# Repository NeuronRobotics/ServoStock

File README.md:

ServoStock
==========

This is the repository for the bowler enabled, closed loop controlled 3d printer. This repository is for all of the code for the printer.

# Control Application

From Eclipse for Java

* https://github.com/NeuronRobotics/java-bowler
* https://github.com/NeuronRobotics/NrConsole
* Jmonkey Game Engine

# Dependancies

## Compiler and c-bowler
Clone the c-bowler repository and install the compilers from here:

* https://github.com/NeuronRobotics/c-bowler

##MPLabx

Install MPLABX from here:

http://www.microchip.com/pagehandler/en-us/family/mplabx/

# Opening projects

Both repositoried should be in the same folder on your disk.

Open c-bowler in MPLABX

```
c-bowler/firmware/library/NR-Clib/development/c-bowler.X
```

And the ServoStock Code

```
ServoStock/firmware/MplabX_Projects/ServoPrinterController.X
```

You are ready to build and program.

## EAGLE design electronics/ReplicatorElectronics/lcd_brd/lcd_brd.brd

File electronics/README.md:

These are the assembly instructions for the ServoStock Electronics platform

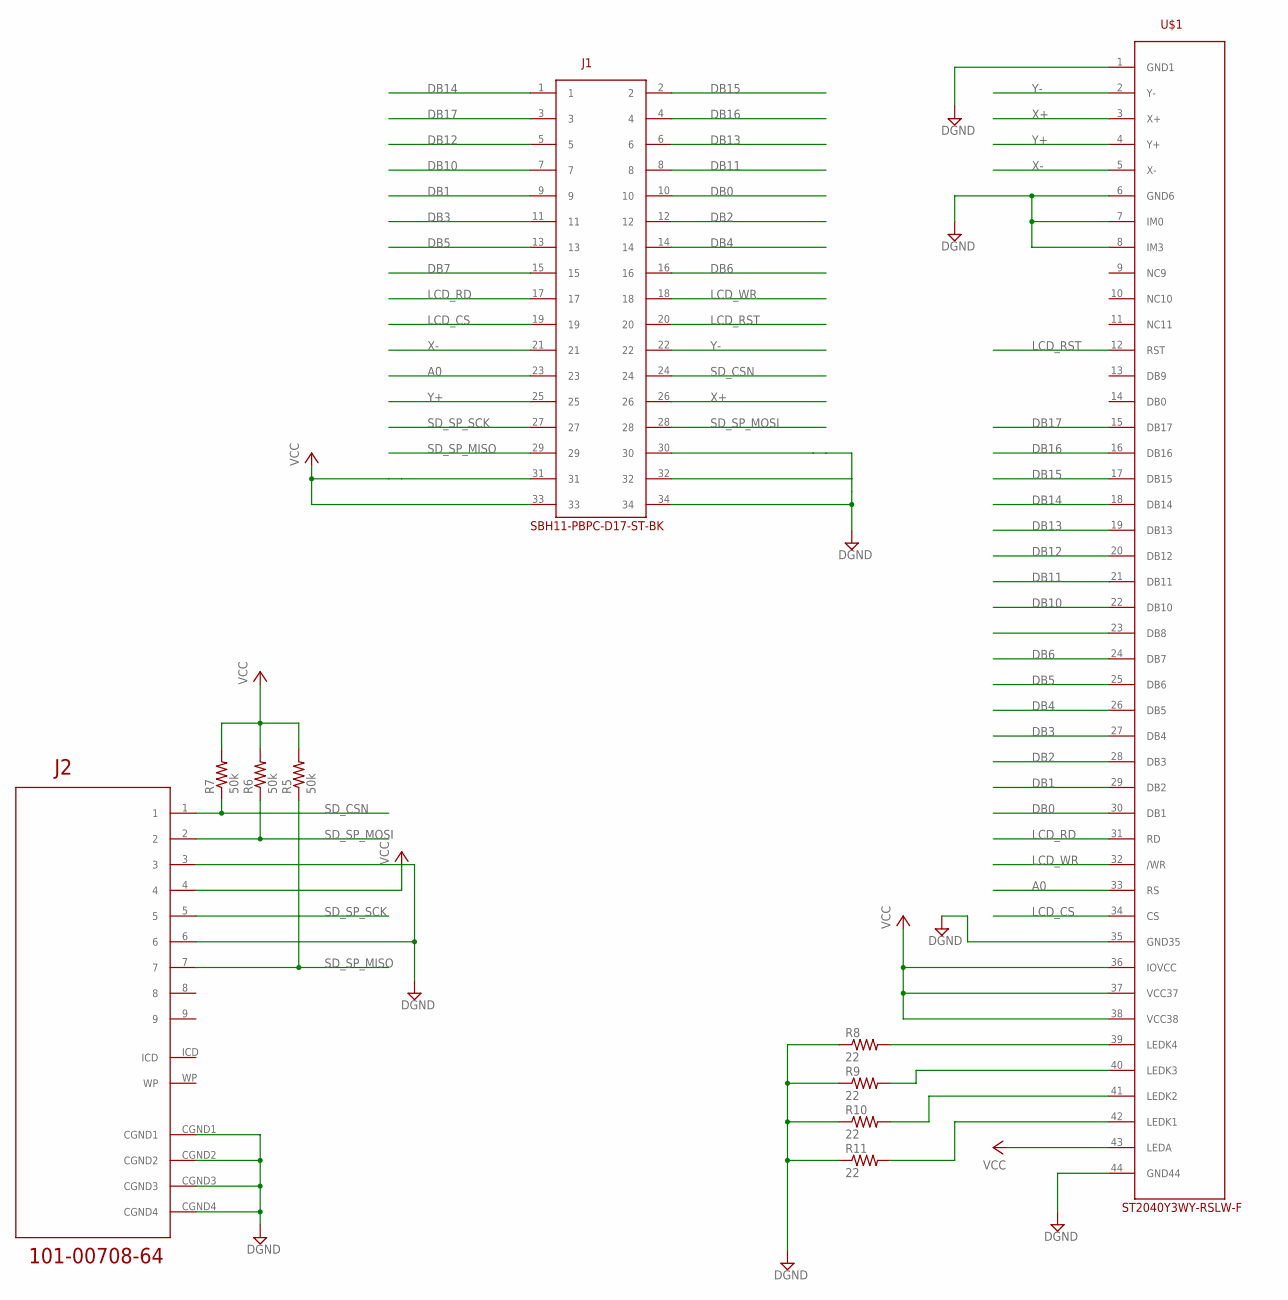
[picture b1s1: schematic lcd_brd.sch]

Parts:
J1: SBH11-PBPC-D17-ST-BK
J2: 101-00708-64
R5, R6, R7: 50k; R0603
R8, R9, R10, R11: 22; R0603
U$1: ST2040Y3WY-RSLW-F; ST0240Y3WY-RSLW-F

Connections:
A0: J1.23, U$1.33 (RS)
DB0: J1.10, U$1.30 (DB1)
DB1: J1.9, U$1.29 (DB2)
DB2: J1.12, U$1.28 (DB3)
DB3: J1.11, U$1.27 (DB4)
DB4: J1.14, U$1.26 (DB5)
DB5: J1.13, U$1.25 (DB6)
DB6: J1.16, U$1.24 (DB7)
DB7: J1.15, U$1.23 (DB8)
DB10: J1.7, U$1.22 (DB10)
DB11: J1.8, U$1.21 (DB11)
DB12: J1.5, U$1.20 (DB12)
DB13: J1.6, U$1.19 (DB13)
DB14: J1.1, U$1.18 (DB14)
DB15: J1.2, U$1.17 (DB15)
DB16: J1.4, U$1.16 (DB16)
DB17: J1.3, U$1.15 (DB17)
DGND: J1.30, J1.32, J1.34, J2.3, J2.6, J2.CGND1, J2.CGND2, J2.CGND3, J2.CGND4, R8.1, R9.1, R10.1, R11.1, U$1.1 (GND1), U$1.6 (GND6), U$1.7 (IM0), U$1.8 (IM3), U$1.35 (GND35), U$1.44 (GND44)
LCD_CS: J1.19, U$1.34 (CS)
LCD_RD: J1.17, U$1.31 (RD)
LCD_RST: J1.20, U$1.12 (RST)
LCD_WR: J1.18, U$1.32 (/WR)
unnamed: R8.2, U$1.39 (LEDK4)
unnamed: R9.2, U$1.40 (LEDK3)
unnamed: R10.2, U$1.41 (LEDK2)
unnamed: R11.2, U$1.42 (LEDK1)
SD_CSN: J1.24, J2.1, R7.1
SD_SP_MISO: J1.29, J2.7, R5.1
SD_SP_MOSI: J1.28, J2.2, R6.1
SD_SP_SCK: J1.27, J2.5
VCC: J1.31, J1.33, J2.4, R5.2, R6.2, R7.2, U$1.36 (IOVCC), U$1.37 (VCC37), U$1.38 (VCC38), U$1.43 (LEDA)
X+: J1.26, U$1.3 (X+)
X-: J1.21, U$1.5 (X-)
Y+: J1.25, U$1.4 (Y+)
Y-: J1.22, U$1.2 (Y-)

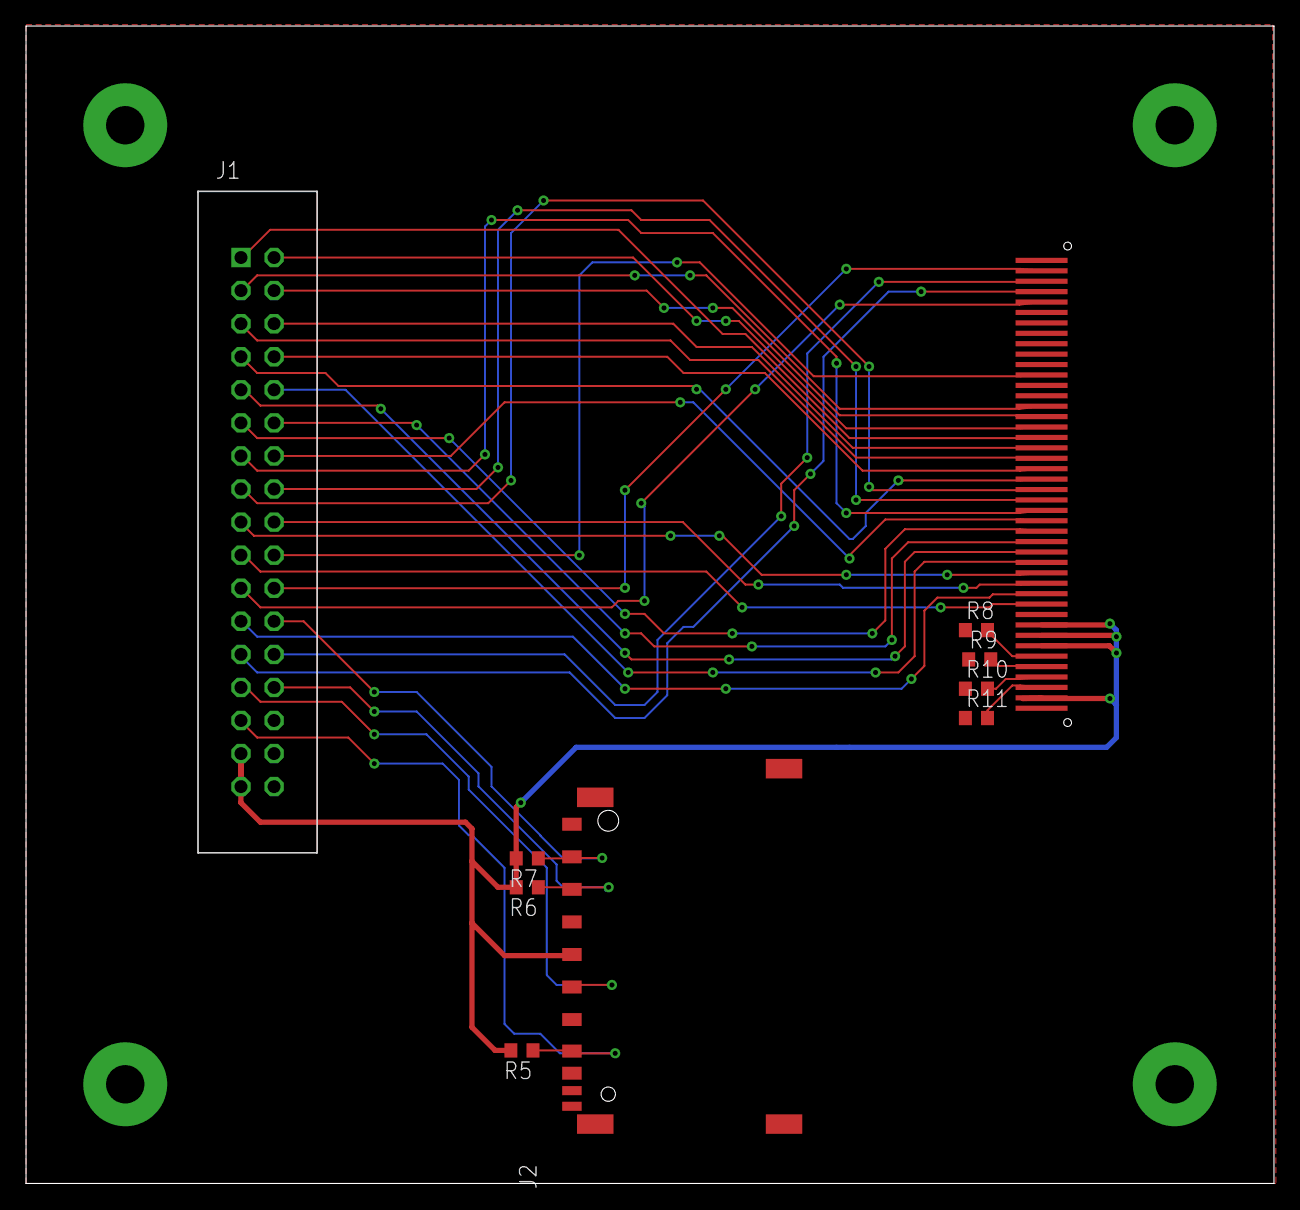
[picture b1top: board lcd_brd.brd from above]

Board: 2 copper layers, 95.8 x 88.9 mm, 10 parts (0 on the bottom side), 35 nets.

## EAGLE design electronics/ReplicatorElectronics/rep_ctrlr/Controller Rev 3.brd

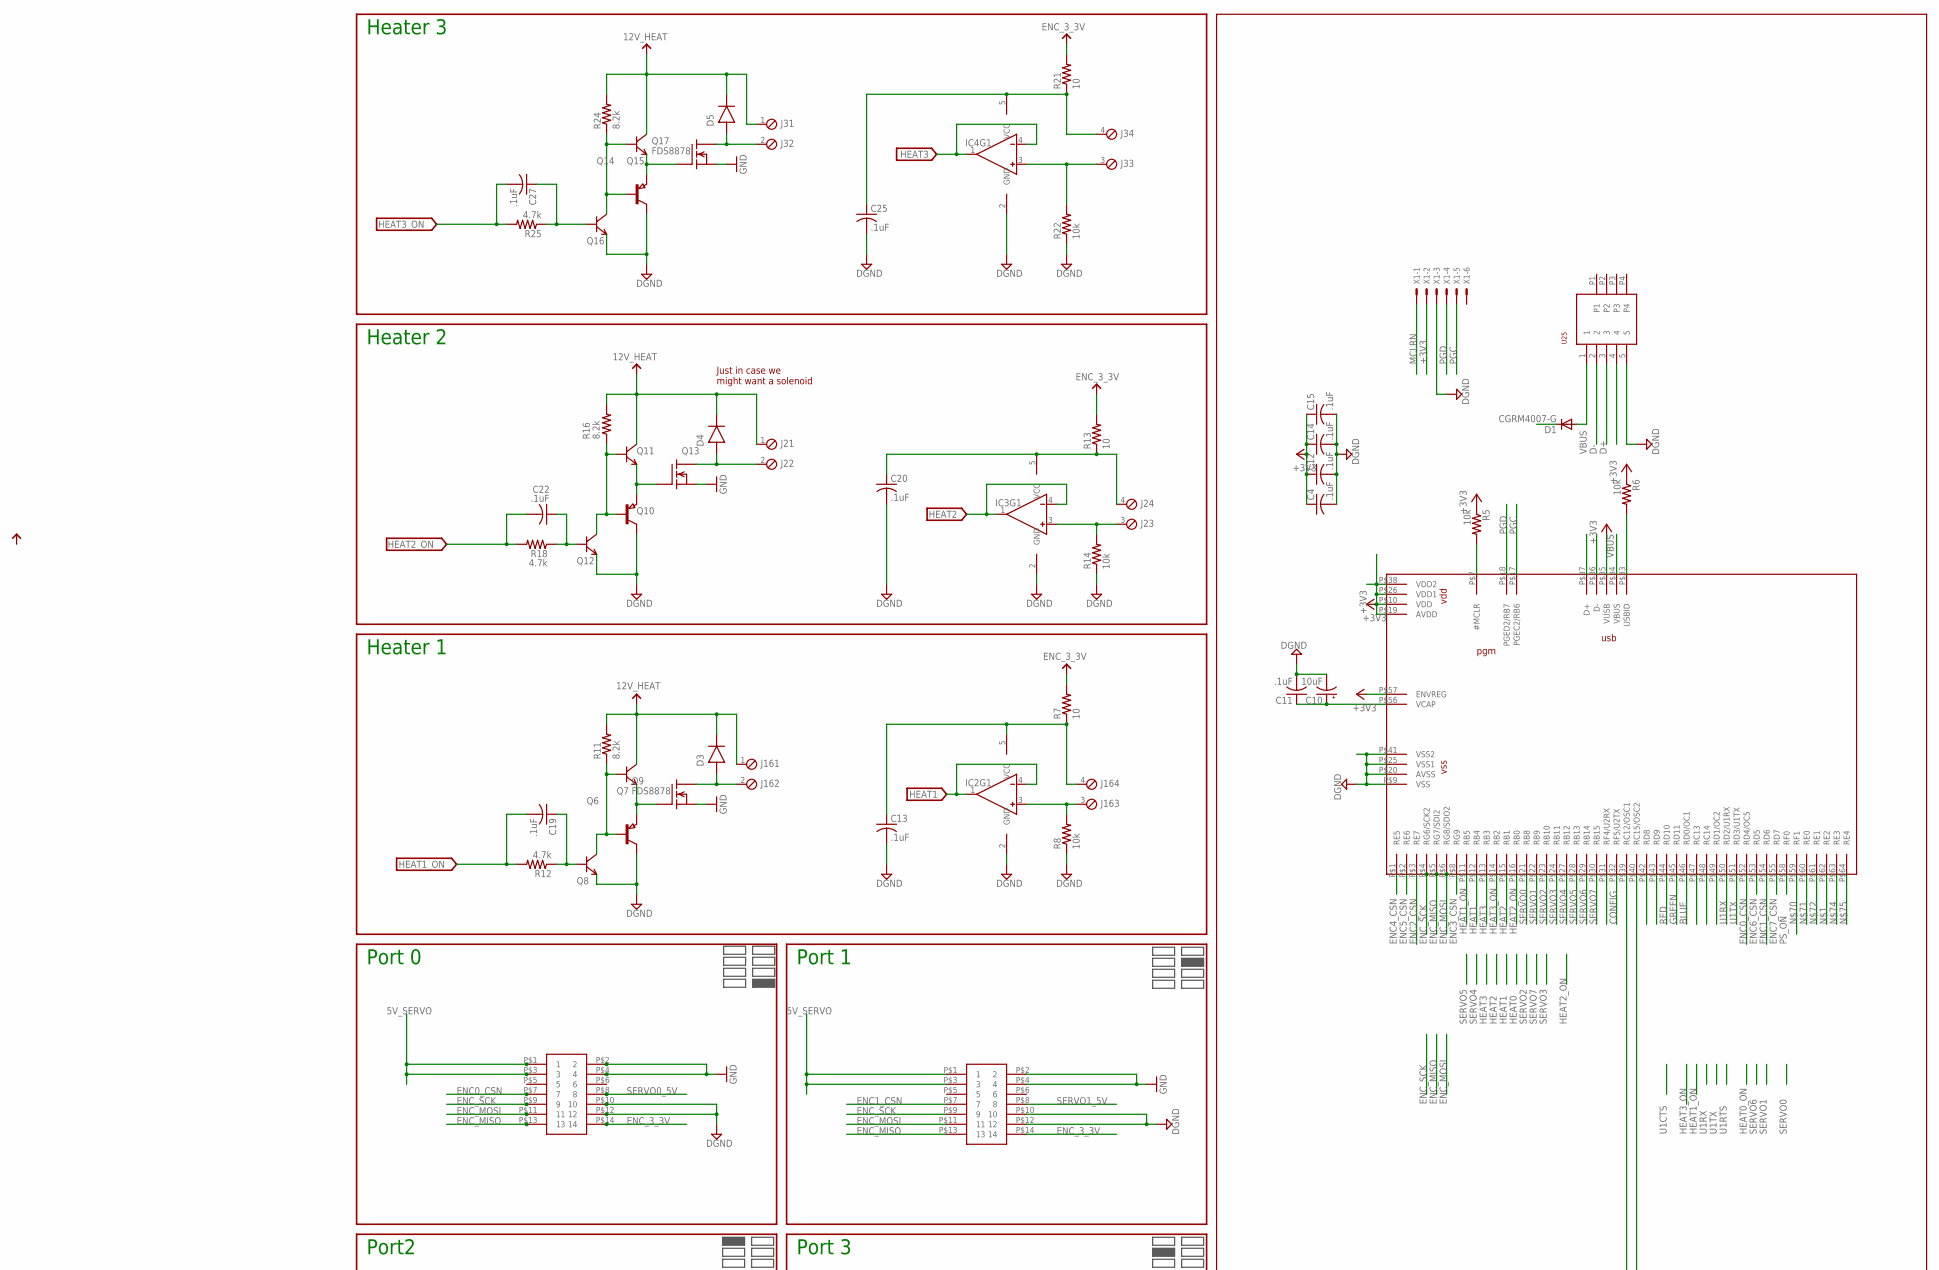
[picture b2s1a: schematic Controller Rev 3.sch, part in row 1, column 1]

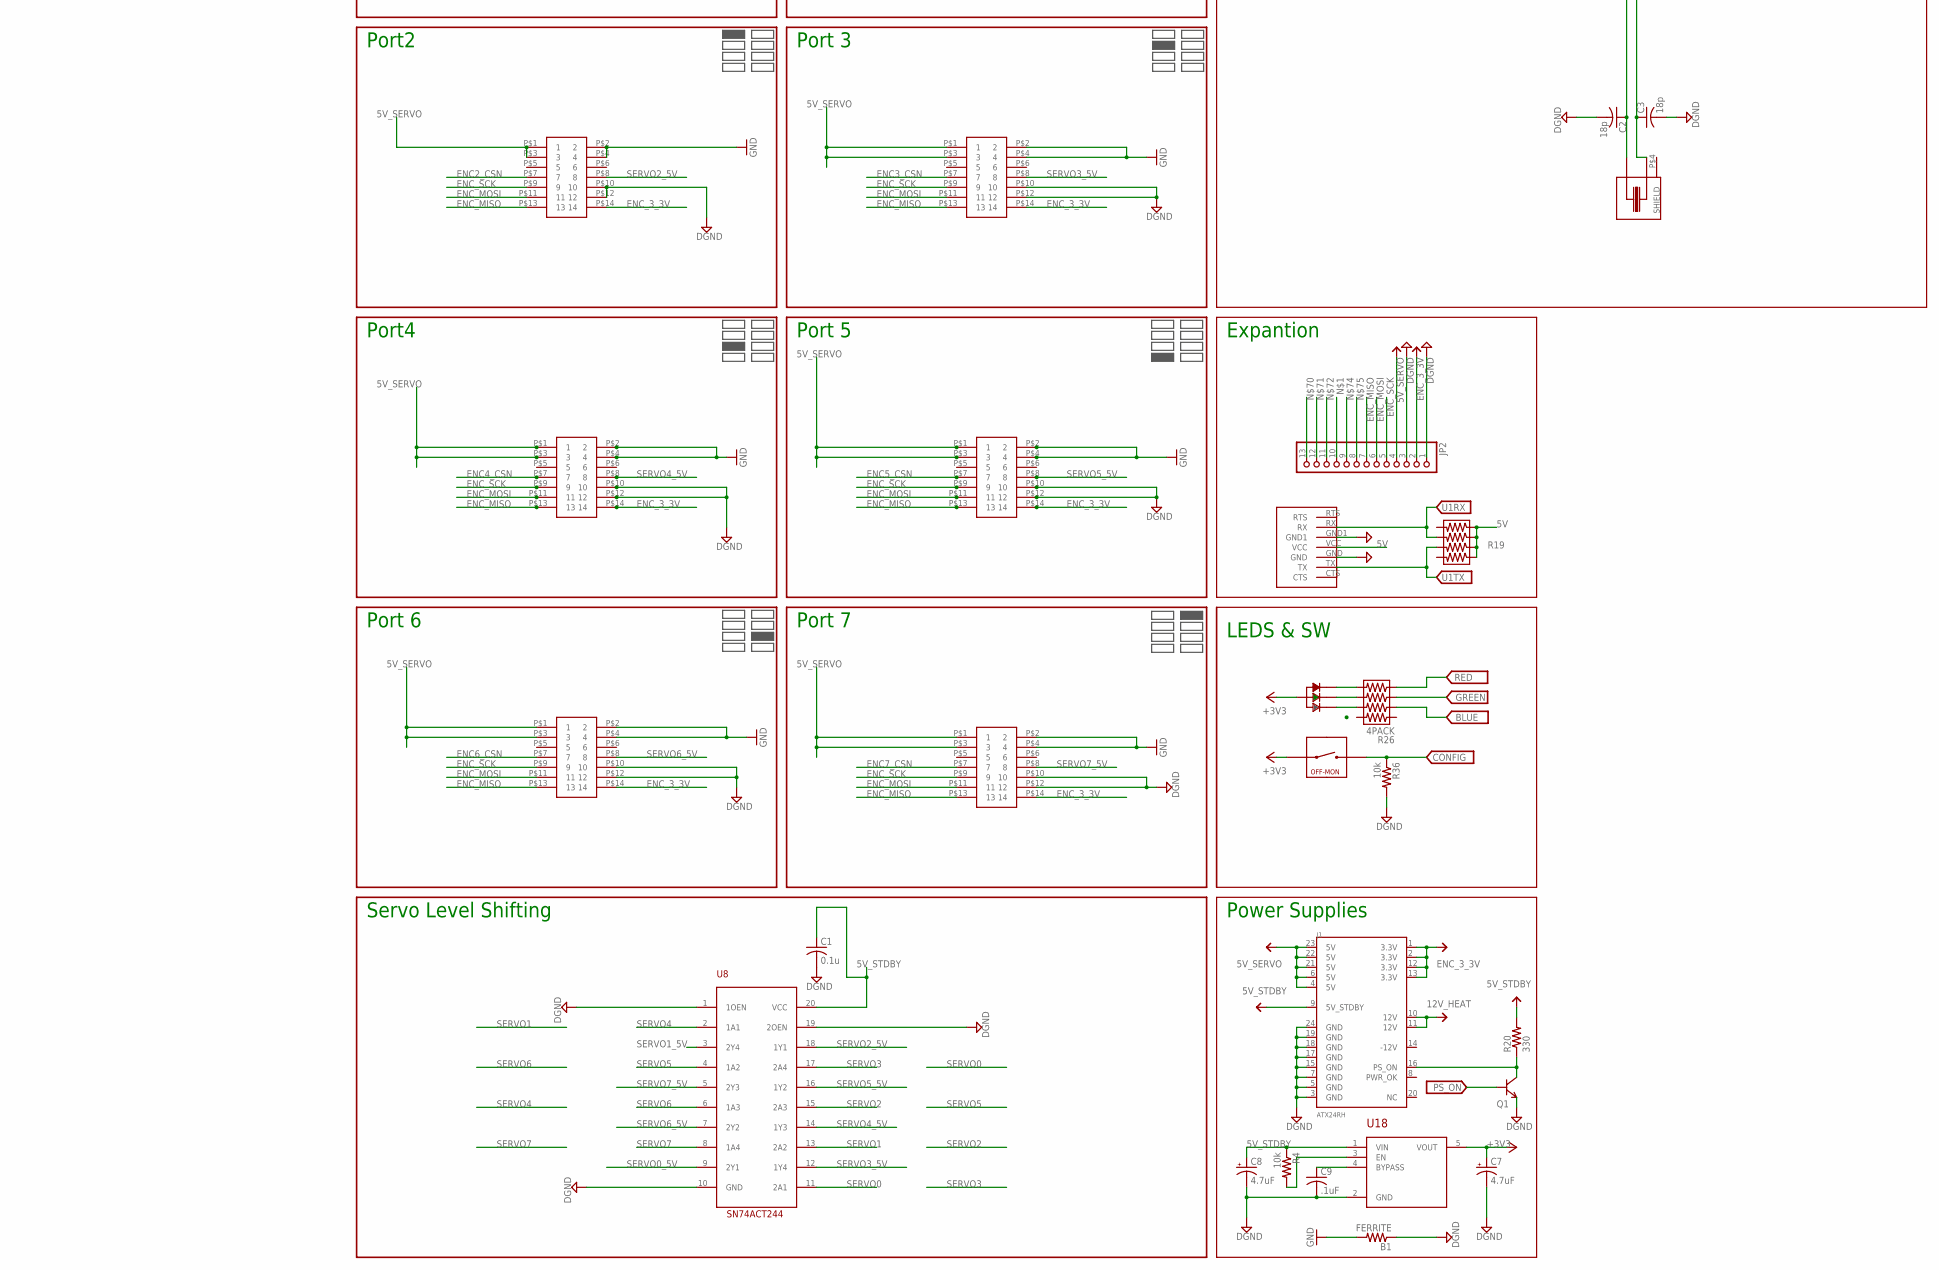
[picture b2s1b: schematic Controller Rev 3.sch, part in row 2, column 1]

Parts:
B1: FERRITE; R0603
C1: 0.1u; C0402
C2, C3: 18p; C0603
C4, C11, C12, C13, C14, C15, C19, C20, C22, C25, C27: .1uF; C0603
C7, C8: 4.7uF; R/2012-12R
C9: .1uF; C0402
C10: 10uF; R/2012-12R
D1: CGRM4007-G; SOD-123_MINI-SMA
D3, D4, D5: DISCRETE_DIODESMA; DISCRETE_SMA
IC2, IC3, IC4: MICROCHIP_MCP6001-LT; MICROCHIP_SC70-5-LT
J1: ATX24RH; ATX24_RIGHT_ANGLE
J2, J3, J16: OSTVN04A150; 4POL254
J10: WASP7PIN
JP2: PINHD-1X13_BIG; 1X13-BIG
Q1, Q7, Q8, Q11, Q12, Q15, Q16: DISCRETE_MMBT3904LT1G; DISCRETE_SOT23
Q6, Q10, Q14: PNP-TRANSISTOR_SOT23; SOT23
Q9, Q13, Q17: FDS8878; SO-8
R4: 10k; R0402
R5, R6, R8, R14, R22, R36: 10k; R0603
R7, R13, R21: 10; R0603
R11, R16, R24: 8.2k; R0603
R12, R18, R25: 4.7k; R0603
R19, R26: 4PACK; 4PACK_0603
R20: 330; R0603
SW3: SPST; B3U-1000P
U1: TRI-LED-SMD; TRI_LED_SMD
U3: PIC32-64TQFP64-2; TQFP64-2
U8: SN74ACT244; 20-SOIC
U18: LDS3985XX33; SOT23-5
U25: 1734035-1_USB; 1734035-1_1734035
U$1, U$2, U$3, U$4, U$5, U$6, U$7, U$8: SBH11-NBPC-D07-SM-BK
X1: 22-23-2061
X2: CMR3XXT; CMR309T

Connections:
5V: J10.VCC, R19.R1B, R19.R2B, R19.R3B, R19.R4B
5V_SERVO: J1.4 (5V), J1.6 (5V), J1.21 (5V), J1.22 (5V), J1.23 (5V), JP2.4, U$1.P$1 (1), U$1.P$3 (3), U$2.P$1 (1), U$2.P$3 (3), U$3.P$1 (1), U$3.P$3 (3), U$4.P$1 (1), U$4.P$3 (3), U$5.P$1 (1), U$5.P$3 (3), U$6.P$1 (1), U$6.P$3 (3), U$7.P$1 (1), U$7.P$3 (3), U$8.P$1 (1), U$8.P$3 (3)
5V_STDBY: C1.1, C8.+, D1.C, J1.9 (5V_STDBY), R4.1, R20.2, U8.20 (VCC), U18.1 (VIN)
12V_HEAT: D3.C, D4.C, D5.C, J1.10 (12V), J1.11 (12V), J2.1, J3.1, J16.1, Q7.3 (C), Q11.3 (C), Q15.3 (C), R11.2, R16.2, R24.2
12V_SW1: D3.A, J16.2, Q9.5 (D), Q9.6 (D), Q9.7 (D), Q9.8 (D)
12V_SW2: D4.A, J2.2, Q13.5 (D), Q13.6 (D), Q13.7 (D), Q13.8 (D)
12V_SW3: D5.A, J3.2, Q17.5 (D), Q17.6 (D), Q17.7 (D), Q17.8 (D)
+3V3: C4.1, C7.+, C12.1, C14.1, C15.1, R5.1, R6.1, SW3.P$1, U1.COMM-A, U3.P$10 (VDD), U3.P$19 (AVDD), U3.P$26 (VDD1), U3.P$35 (VUSB), U3.P$38 (VDD2), U3.P$57 (ENVREG), U18.5 (VOUT), X1.2
B: R26.R2A, U1.BLUE
BLUE: R26.R2B, U3.P$46 (RD0/OC1)
CONFIG: R36.1, SW3.P$3, U3.P$32 (RF5/U2TX)
D+: U3.P$37 (D+), U25.3
D-: U3.P$36 (D-), U25.2
DGND: B1.1, C1.2, C2.2, C3.2, C4.2, C7.-, C8.-, C9.2, C10.-, C11.2, C12.2, C13.2, C14.2, C15.2, C20.2, C25.2, IC2.2 (GND), IC3.2 (GND), IC4.2 (GND), J1.3 (GND), J1.5 (GND), J1.7 (GND), J1.15 (GND), J1.17 (GND), J1.18 (GND), J1.19 (GND), J1.24 (GND), J10.GND, J10.GND1, JP2.1, JP2.3, Q1.2 (E), Q6.3 (C), Q8.2 (E), Q10.3 (C), Q12.2 (E), Q14.3 (C), Q16.2 (E), R8.1, R14.1, R22.1, R36.2, U3.P$9 (VSS), U3.P$20 (AVSS), U3.P$25 (VSS1), U3.P$41 (VSS2), U8.1 (1OEN), U8.10 (GND), U8.19 (2OEN), U18.2 (GND), U25.5, U$1.P$10 (10), U$1.P$12 (12), U$2.P$10 (10), U$2.P$12 (12), U$3.P$10 (10), U$3.P$12 (12), U$4.P$10 (10), U$4.P$12 (12), U$5.P$10 (10), U$5.P$12 (12), U$6.P$10 (10), U$6.P$12 (12), U$7.P$10 (10), U$7.P$12 (12), U$8.P$10 (10), U$8.P$12 (12), X1.3
ENC0_CSN: U3.P$52 (RD4/OC5), U$8.P$7 (7)
ENC1_CSN: U3.P$54 (RD6), U$6.P$7 (7)
ENC2_CSN: U3.P$3 (RE7), U$1.P$7 (7)
ENC3_CSN: U3.P$8 (RG9), U$2.P$7 (7)
ENC4_CSN: U3.P$1 (RE5), U$3.P$7 (7)
ENC5_CSN: U3.P$2 (RE6), U$4.P$7 (7)
ENC6_CSN: U3.P$53 (RD5), U$7.P$7 (7)
ENC7_CSN: U3.P$55 (RD7), U$5.P$7 (7)
ENC_3_3V: J1.1 (3.3V), J1.2 (3.3V), J1.12 (3.3V), J1.13 (3.3V), JP2.2, R7.2, R13.2, R21.2, U$1.P$14 (14), U$2.P$14 (14), U$3.P$14 (14), U$4.P$14 (14), U$5.P$14 (14), U$6.P$14 (14), U$7.P$14 (14), U$8.P$14 (14)
ENC_MISO: JP2.7, U3.P$5 (RG7/SDI2), U$1.P$13 (13), U$2.P$13 (13), U$3.P$13 (13), U$4.P$13 (13), U$5.P$13 (13), U$6.P$13 (13), U$7.P$13 (13), U$8.P$13 (13)
ENC_MOSI: JP2.6, U3.P$6 (RG8/SDO2), U$1.P$11 (11), U$2.P$11 (11), U$3.P$11 (11), U$4.P$11 (11), U$5.P$11 (11), U$6.P$11 (11), U$7.P$11 (11), U$8.P$11 (11)
ENC_SCK: JP2.5, U3.P$4 (RG6/SCK2), U$1.P$9 (9), U$2.P$9 (9), U$3.P$9 (9), U$4.P$9 (9), U$5.P$9 (9), U$6.P$9 (9), U$7.P$9 (9), U$8.P$9 (9)
G: R26.R3A, U1.GRN
GND: B1.2, Q9.1 (S), Q9.2 (S), Q9.3 (S), Q13.1 (S), Q13.2 (S), Q13.3 (S), Q17.1 (S), Q17.2 (S), Q17.3 (S), U$1.P$2 (2), U$1.P$4 (4), U$2.P$2 (2), U$2.P$4 (4), U$3.P$2 (2), U$3.P$4 (4), U$4.P$2 (2), U$4.P$4 (4), U$5.P$2 (2), U$5.P$4 (4), U$6.P$2 (2), U$6.P$4 (4), U$7.P$2 (2), U$7.P$4 (4), U$8.P$2 (2), U$8.P$4 (4)
GREEN: R26.R3B, U3.P$45 (RD11)
HEAT1: IC2.1 (OUT), IC2.4 (IN-), U3.P$12 (RB4)
HEAT1_ON: C19.2, R12.2, U3.P$11 (RB5)
HEAT2: IC3.1 (OUT), IC3.4 (IN-), U3.P$15 (RB1)
HEAT2_ON: C22.2, R18.2, U3.P$16 (RB0)
HEAT3: IC4.1 (OUT), IC4.4 (IN-), U3.P$13 (RB3)
HEAT3_ON: C27.2, R25.2, U3.P$14 (RB2)
MCLRN: R5.2, U3.P$7 (#MCLR), X1.1
unnamed: JP2.10, U3.P$62 (RE2)
unnamed: R4.2, U18.3 (EN)
unnamed: C9.1, U18.4 (BYPASS)
unnamed: C3.1, U3.P$40 (RC15/OSC2), X2.P$3
unnamed: C10.+, C11.1, U3.P$56 (VCAP)
unnamed: C2.1, U3.P$39 (RC12/OSC1), X2.P$1
unnamed: IC2.3 (IN+), J16.3, R8.2
unnamed: C13.1, IC2.5 (VCC), J16.4, R7.1
unnamed: Q6.1 (B), Q7.1 (B), Q8.3 (C), R11.1
unnamed: C19.1, Q8.1 (B), R12.1
unnamed: Q6.2 (E), Q7.2 (E), Q9.4 (G)
unnamed: IC3.3 (IN+), J2.3, R14.2
unnamed: C20.1, IC3.5 (VCC), J2.4, R13.1
unnamed: Q10.1 (B), Q11.1 (B), Q12.3 (C), R16.1
unnamed: C22.1, Q12.1 (B), R18.1
unnamed: Q10.2 (E), Q11.2 (E), Q13.4 (G)
unnamed: IC4.3 (IN+), J3.3, R22.2
unnamed: C25.1, IC4.5 (VCC), J3.4, R21.1
unnamed: Q14.1 (B), Q15.1 (B), Q16.3 (C), R24.1
unnamed: C27.1, Q16.1 (B), R25.1
unnamed: Q14.2 (E), Q15.2 (E), Q17.4 (G)
unnamed: J1.16 (PS_ON), Q1.3 (C), R20.1
unnamed: JP2.13, U3.P$59 (RF1)
unnamed: JP2.12, U3.P$60 (RE0)
unnamed: JP2.11, U3.P$61 (RE1)
unnamed: JP2.9, U3.P$63 (RE3)
unnamed: JP2.8, U3.P$64 (RE4)
PGC: U3.P$17 (PGEC2/RB6), X1.5
PGD: U3.P$18 (PGED2/RB7), X1.4
PS_ON: Q1.1 (B), U3.P$58 (RF0)
R: R26.R4A, U1.RED
RED: R26.R4B, U3.P$44 (RD10)
SERVO0: U3.P$21 (RB8), U8.11 (2A1)
SERVO0_5V: U8.9 (2Y1), U$8.P$8 (8)
SERVO1: U3.P$22 (RB9), U8.13 (2A2)
SERVO1_5V: U8.3 (2Y4), U$6.P$8 (8)
SERVO2: U3.P$23 (RB10), U8.15 (2A3)
SERVO2_5V: U8.18 (1Y1), U$1.P$8 (8)
SERVO3: U3.P$24 (RB11), U8.17 (2A4)
SERVO3_5V: U8.12 (1Y4), U$2.P$8 (8)
SERVO4: U3.P$27 (RB12), U8.2 (1A1)
SERVO4_5V: U8.14 (1Y3), U$3.P$8 (8)
SERVO5: U3.P$28 (RB13), U8.4 (1A2)
SERVO5_5V: U8.16 (1Y2), U$4.P$8 (8)
SERVO6: U3.P$29 (RB14), U8.6 (1A3)
SERVO6_5V: U8.7 (2Y2), U$7.P$8 (8)
SERVO7: U3.P$30 (RB15), U8.8 (1A4)
SERVO7_5V: U8.5 (2Y3), U$5.P$8 (8)
U1RX: J10.RX, R19.R2A, U3.P$50 (RD2/U1RX)
U1TX: J10.TX, R19.R3A, U3.P$51 (RD3/U1TX)
USBID: R6.2, U3.P$33 (USBID), U25.4
VBUS: D1.A, U3.P$34 (VBUS), U25.1

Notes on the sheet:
Just in case we might want a solenoid
Heater 2
Heater 1
Heater 3
LEDS & SW
Power Supplies
Servo Level Shifting
Port 6
Port 7
Port 5
Port4
Port2
Port 3
Port 1
Port 0
Expantion

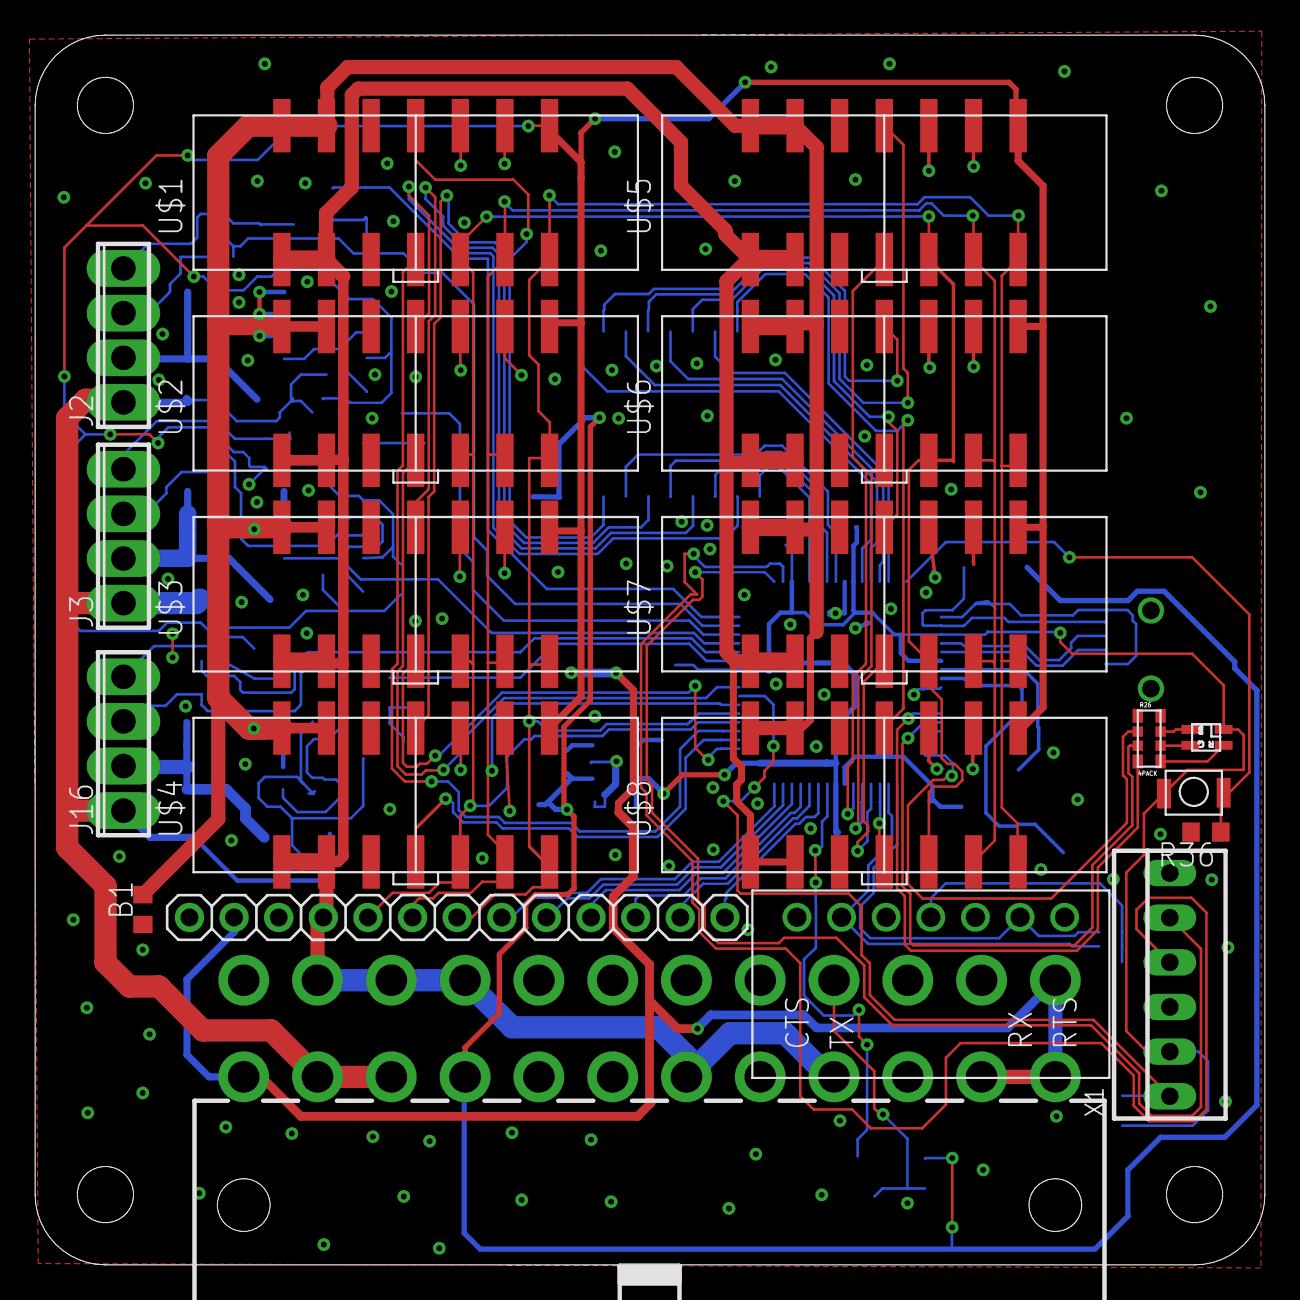
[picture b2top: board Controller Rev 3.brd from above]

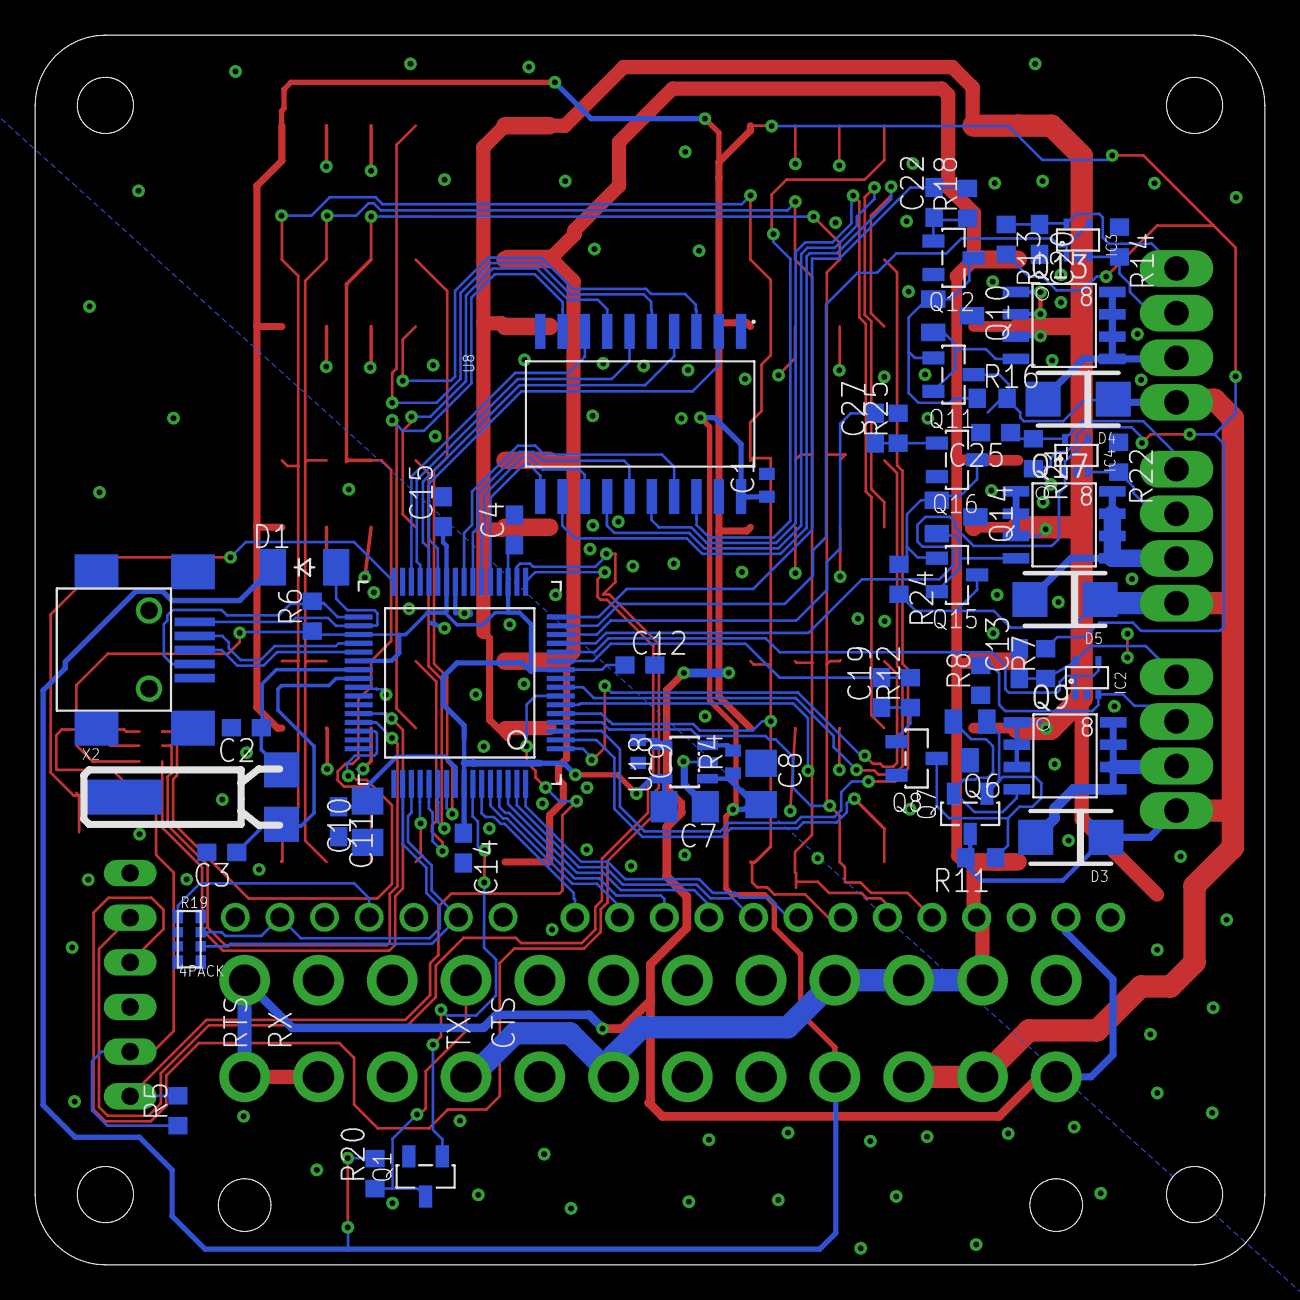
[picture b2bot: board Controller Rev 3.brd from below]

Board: 2 copper layers, 70.0 x 70.0 mm, 81 parts (60 on the bottom side), 88 nets.

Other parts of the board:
U$9: DP7070_V1

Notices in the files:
ReplicatorFirmware/NR-Clib/include/arch/pic32/HardwareProfile.h:
Copyright (C) 2002-2008 Microchip Technology Inc.  All rights
parts and their libraries:
SparkFun-Connectors: Licensing: CC v3.0 Share-Alike You are welcome to use this library for commercial purposes.
SMSC8720a_Ethernet_PHY: Footprint made by Alex Camilo. CC BY SA
